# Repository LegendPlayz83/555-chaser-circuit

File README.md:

# 555-chaser-circuit
A 555 chaser circuit with LEDs, Resistors, Microcontrollers and more

# PCB view:

# Cart

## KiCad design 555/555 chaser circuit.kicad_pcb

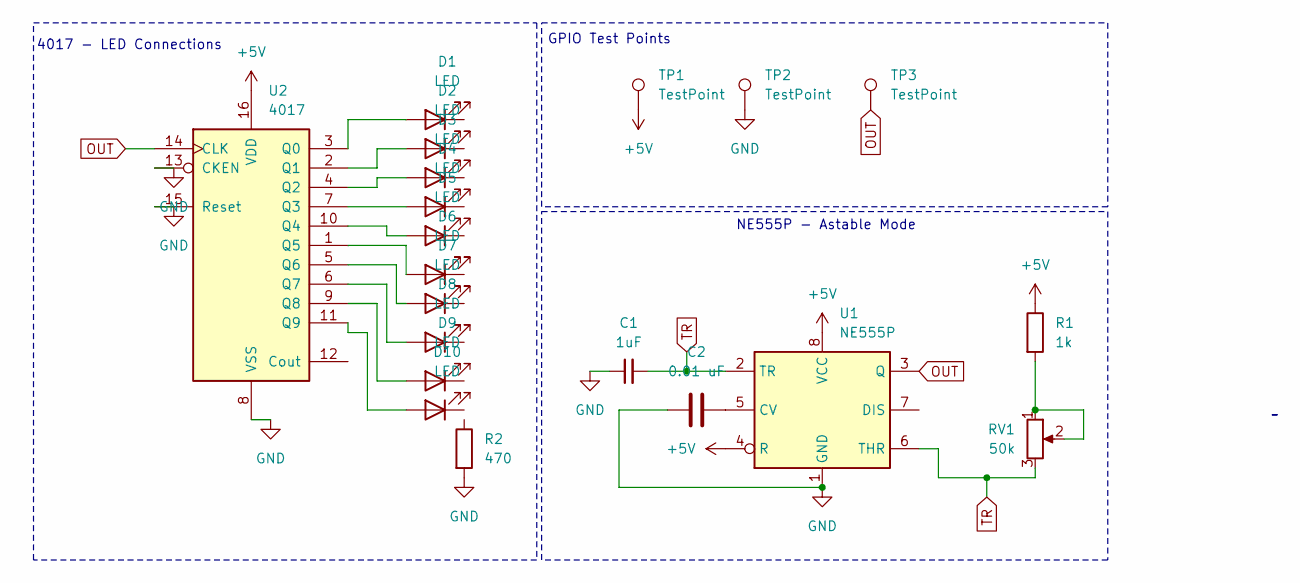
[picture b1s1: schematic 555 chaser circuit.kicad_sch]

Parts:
C1: 1uF_0201_4V; CP_Radial_D5.0mm_P2.00mm; Part Number CC0201MRX5R5BB105; JLCPCB ID C272877
C2: 0.01 uF; CP_Radial_D5.0mm_P2.00mm
D1, D2, D3, D4, D5, D6, D7, D8, D9, D10: LED; LED_D3.0mm
R1: 1k; R_Axial_DIN0207_L6.3mm_D2.5mm_P7.62mm_Horizontal
R2: 470; R_Axial_DIN0207_L6.3mm_D2.5mm_P7.62mm_Horizontal
RV1: 50k; Potentiometer_Bourns_3296W_Vertical
TP1, TP2, TP3: TestPoint; PinSocket_1x01_P2.54mm_Horizontal
U1: NE555P; DIP-8_W7.62mm
U2: 4017; N16

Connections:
+5V: R1.1, TP1.1, U1.4 (R), U1.8 (VCC), U2.16 (VDD)
GND: C1.1, C2.1, R2.2, TP2.1, U1.1 (GND), U2.8 (VSS), U2.13 (CKEN), U2.15 (Reset)
unnamed: D1.2 (A), U2.3 (Q0)
unnamed: D2.2 (A), U2.2 (Q1)
unnamed: D3.2 (A), U2.4 (Q2)
unnamed: D4.2 (A), U2.7 (Q3)
unnamed: D5.2 (A), U2.10 (Q4)
unnamed: D6.2 (A), U2.1 (Q5)
unnamed: D7.2 (A), U2.5 (Q6)
unnamed: D8.2 (A), U2.6 (Q7)
unnamed: D9.2 (A), U2.9 (Q8)
unnamed: D10.2 (A), U2.11 (Q9)
unnamed: R1.2, RV1.1, RV1.2
unnamed: C2.2, U1.5 (CV)
OUT: TP3.1, U1.3 (Q), U2.14 (CLK)
TR: C1.2, RV1.3, U1.2 (TR), U1.6 (THR)

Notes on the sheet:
NE555P - Astable Mode
4017 - LED Connections
GPIO Test Points

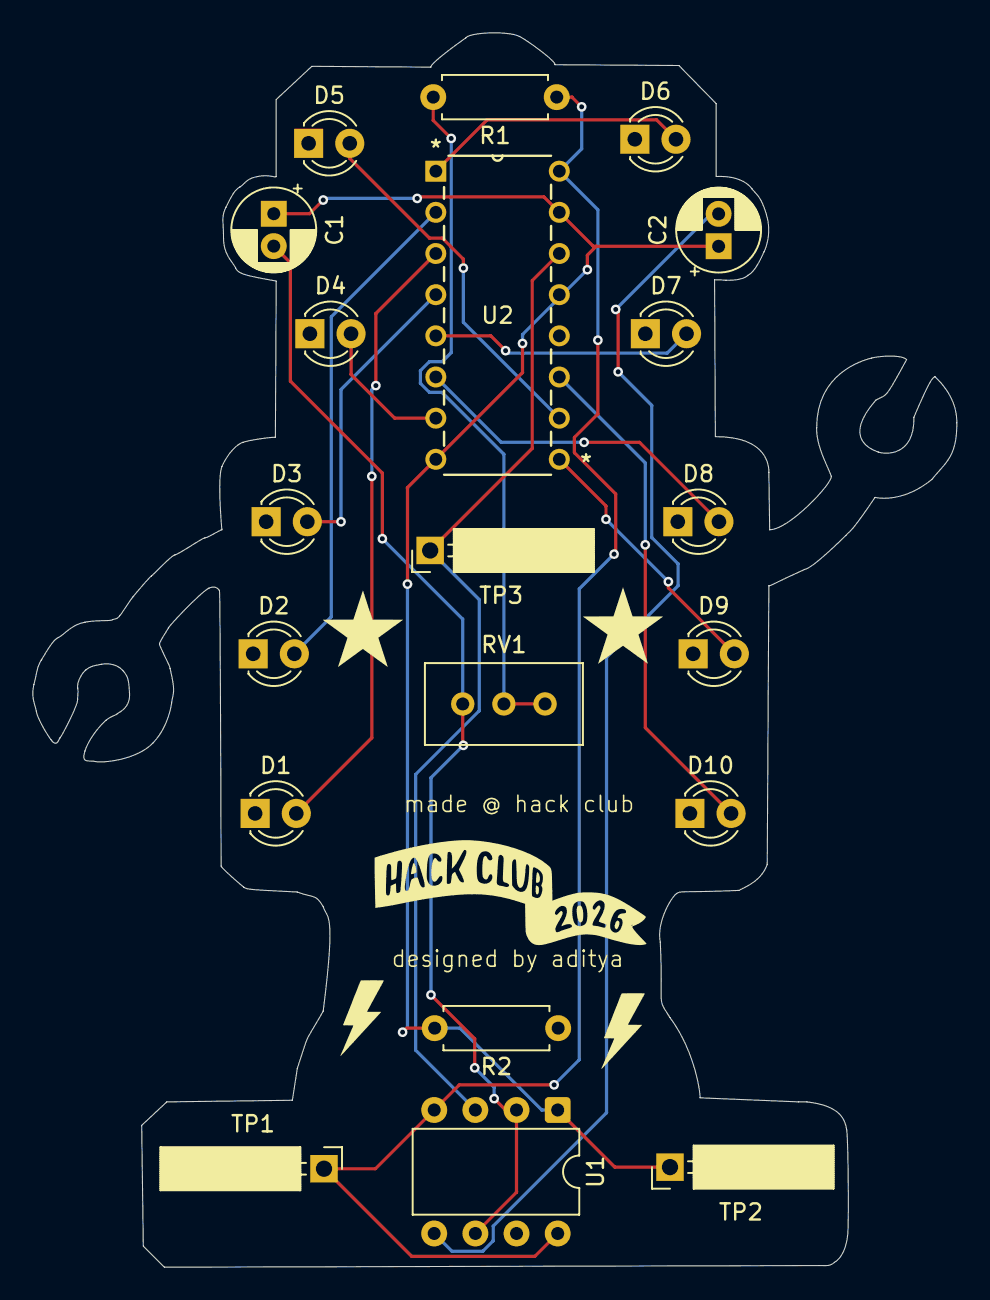
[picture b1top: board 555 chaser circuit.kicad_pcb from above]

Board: 2 copper layers, 57.0 x 76.2 mm, 20 parts (0 on the bottom side), 16 nets.

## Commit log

2026-02-03 Add images to README for 3D and PCB views
    Added images for 3D view and PCB view.
2026-02-03 Add cart section with image to README
    Added cart image to the README file.
